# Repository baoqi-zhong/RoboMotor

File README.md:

# RoboMotor

**English** | [中文版](./README_CN.md)

**RoboMotor** is an open-source FOC motor driver project. It provides integrated hardware designs and control algorithms for robotics applications.

## Key Features

- **Hardware Specs**: 4-to-6 layer PCBs designed for 20A-40A continuous current at 24V.
- **Control Algorithm**: Field-Oriented Control (FOC) with current, speed, and position loops.
- **Validation**: Designs tested in RoboMaster environments.

## Hardware

Designed with **KiCad 8**.
For detailed specifications, schematics, and measured performance, please visit the [Hardware](./Hardware/README.md) directory or click on a specific project below.

| Project Name | Target Motor | Key Specs | Core |
| :--- | :--- | :--- | :--- |
| [**RoboMotor-DJI-M3508**](./Hardware/RoboMotor-DJI-M3508/) | [DJI M3508](https://www.robomaster.com/en-US/products/components/general/M3508) | **24V 20A**, 6-Layer, Sin/Cos Encoder | STSPIN32G4 |
| [**RoboMotor-GIM6010-V2**](./Hardware/RoboMotor-GIM6010-V2/) | [GIM6010-8](https://steadywin-motor.com/products/built-in-star-gear-motor-motor-robot-joint-driver-actuator-controller-motor) | **24V 40A**, Dual Encoder Support | STSPIN32G4 |
| [**RoboMotor-GIM6010-V2-Encoder**](./Hardware/RoboMotor-GIM6010-V2-Encoder/) | GIM6010-8 | Magnetic Output Encoder PCB | MA730 |
| [**RoboMotor-GIM6010**](./Hardware/RoboMotor-GIM6010/) | GIM6010-8 | *Legacy Reference Design* | STM32G431 + FD6288 |

## Software

The FOC control algorithm is developed for the **STM32G4** series.

### Features
- **FOC Implementation**: Sensor-based Field-Oriented Control with Flux/Torque decoupling and BEMF feedforward compensation.
- **Control Loops**: 17Khz inner Current loop + outer 4Khz Speed loop + 1Khz Position loop.
- **Connectivity**:
  - **CAN Bus**: Compatible with DJI RoboMaster protocols (M3508/C620).
  - **Custom Protocol**: Extended commands for parameter tuning and telemetry.
- **Additional Functions**:
  - **Auto-Calibration**: Routines for encoder offset and motor parameter identification.
  - **Safety Mechanisms**: Error handling (Over-current, Over/under voltage, Over-temp) with auto-recovery modes.
  - **Feedback Support**: Support for SPI magnetic encoders and analog inputs.

*Find the source code and documentation in the `Software/` directory.*

## License

This project is released under the MIT License.  
See [LICENSE](./LICENSE) for details.

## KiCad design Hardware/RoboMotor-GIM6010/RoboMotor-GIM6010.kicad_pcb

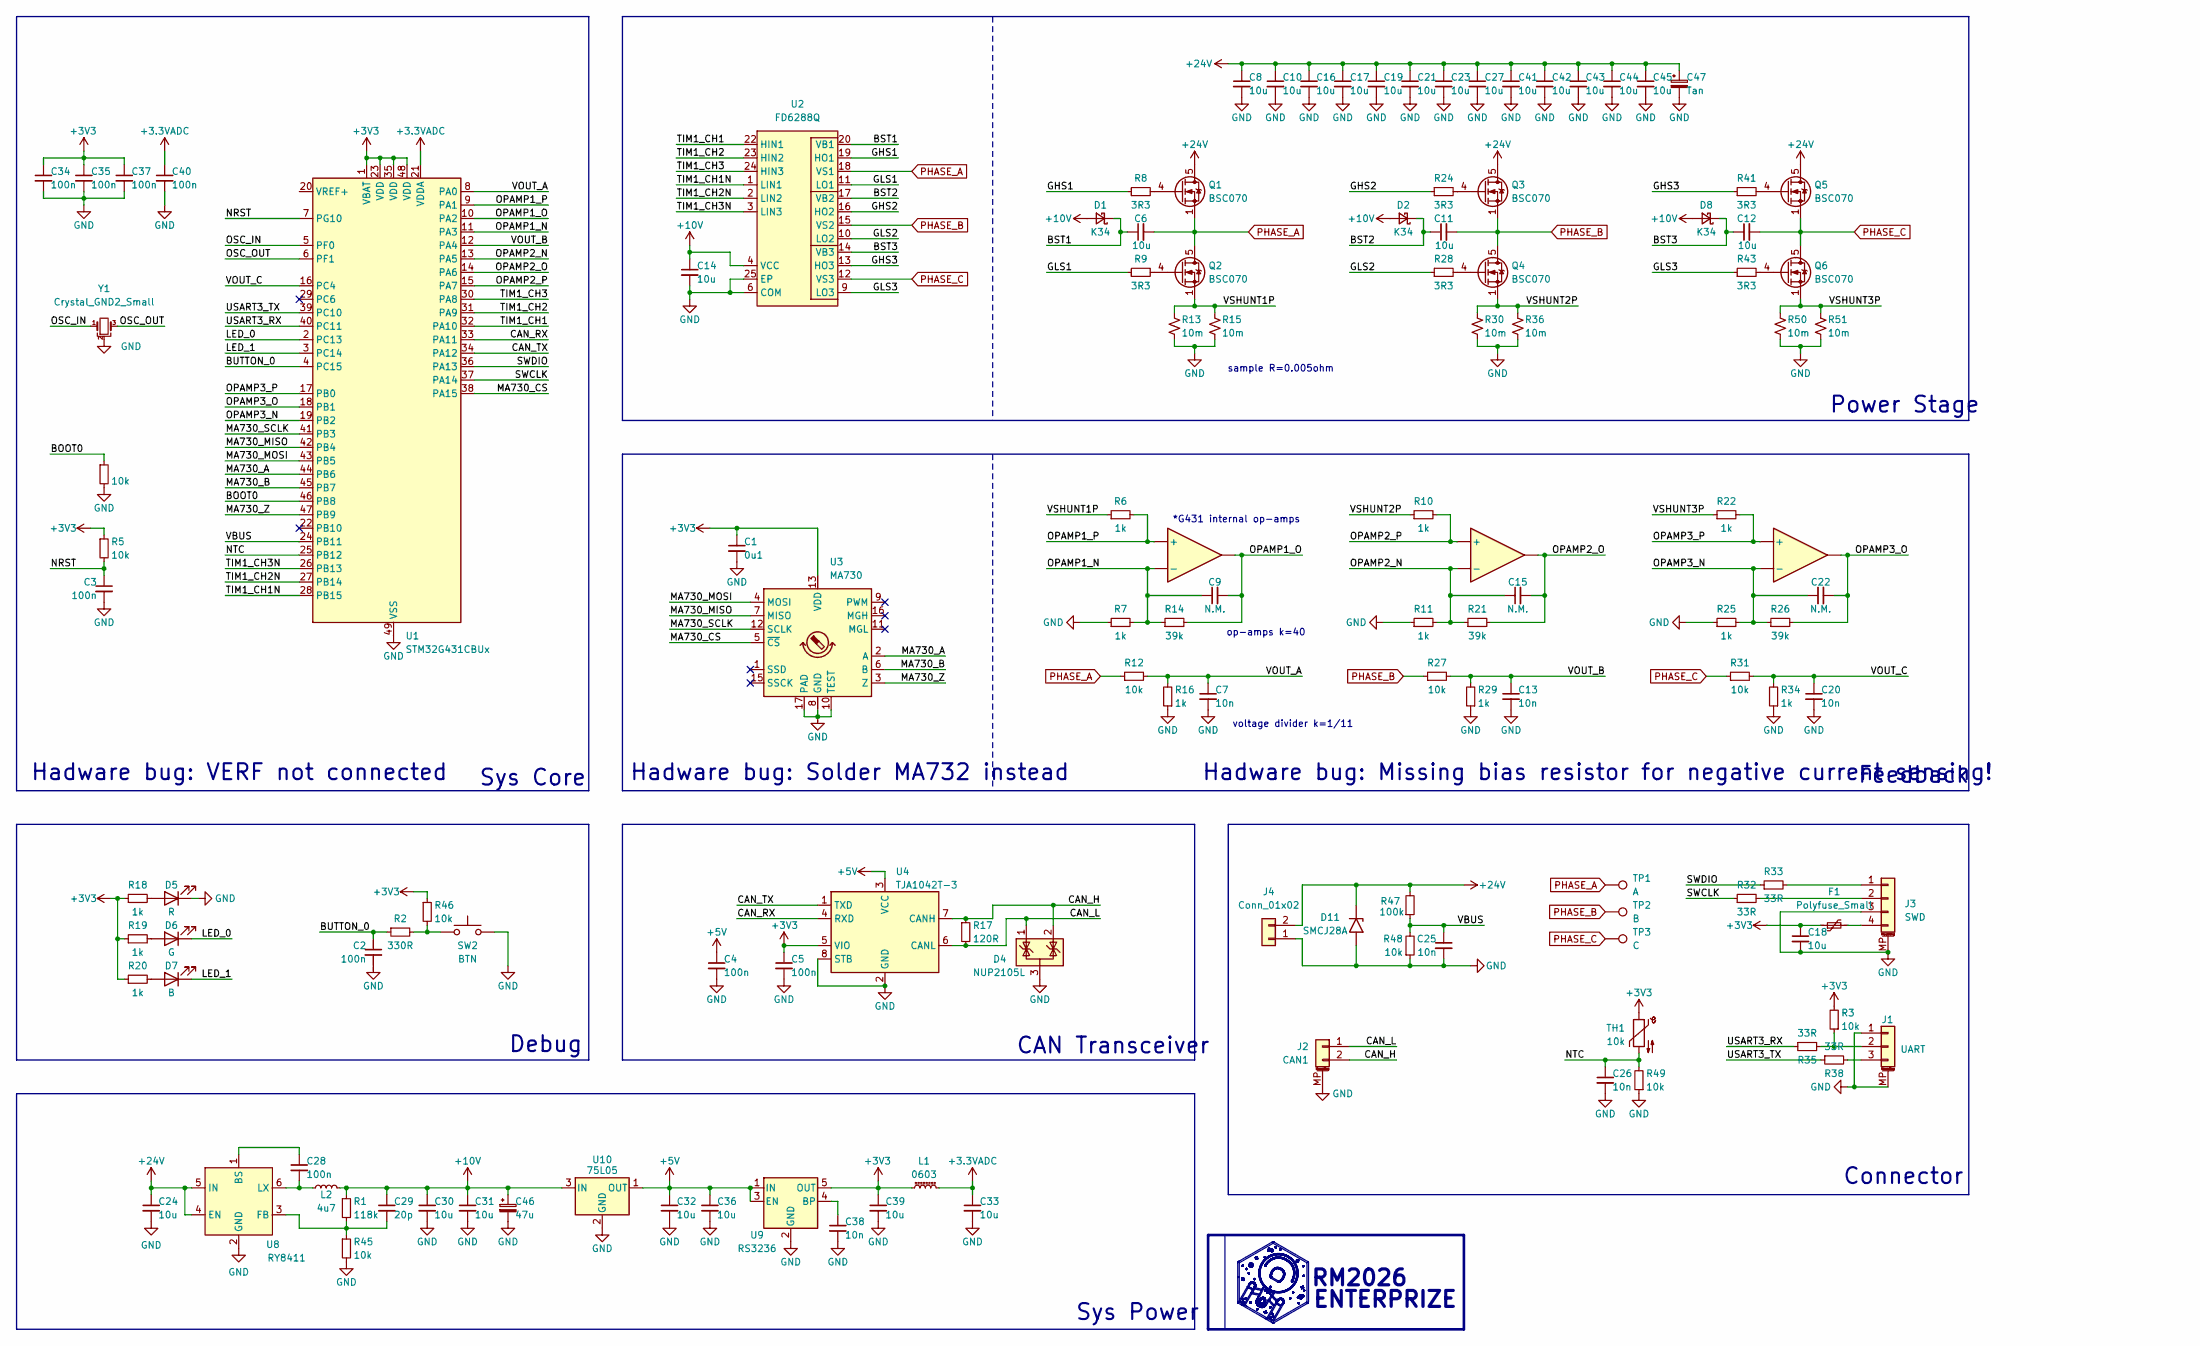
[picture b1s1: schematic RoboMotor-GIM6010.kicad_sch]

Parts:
C1: 0u1; C_0603_1608Metric
C2, C3, C4, C5, C28, C34, C35, C37, C40: 100n; C_0603_1608Metric
C6, C11, C12, C14, C18, C32, C33, C36, C39: 10u; C_0603_1608Metric
C7, C13, C20, C25, C26, C38: 10n; C_0603_1608Metric
C8, C10, C16, C17, C19, C21, C23, C24, C27, C30, C31, C41, C42, C43, C44, C45: 10u; C_1206_3216Metric
C9, C15, C22: N.M.; C_0603_1608Metric
C29: 20p; C_0603_1608Metric
C46: 47u; CP_EIA-3216-18_Kemet-A_Pad1.58x1.35mm_HandSolder
C47: Tan; CP_EIA-7343-30_AVX-N
D1, D2, D8: K34; D_SOD-323_HandSoldering
D4: NUP2105L; SOT-23
D5: R; LED_Side_0802
D6: G; LED_Side_0802
D7: B; LED_Side_0802
D11: SMCJ28A; D_SMC
F1: Polyfuse_Small; Fuse_1206_3216Metric
J1: UART; JST_GH_SM03B-GHS-TB_1x03-1MP_P1.25mm_Horizontal
J2: CAN1; JST_GH_SM02B-GHS-TB_1x02-1MP_P1.25mm_Horizontal
J3: SWD; Molex_PicoBlade_53261-0471_1x04-1MP_P1.25mm_Horizontal
J4: Conn_01x02; AMASS_XT30PW-M_1x02_P2.50mm_Horizontal
L1: 0603; L_0603_1608Metric
L2: 4u7; L_Sunlord_MWSA0402S
Q1, Q2, Q3, Q4, Q5, Q6: BSC070; TDSON-8-1
R1: 118k; R_0603_1608Metric
R2: 330R; R_0603_1608Metric
R3, R4, R5, R12, R27, R31, R45, R46, R48, R49: 10k; R_0603_1608Metric
R6, R7, R10, R11, R16, R18, R19, R20, R22, R25, R29, R34: 1k; R_0603_1608Metric
R8, R9, R24, R28, R41, R43: 3R3; R_0603_1608Metric
R13, R15, R30, R36, R50, R51: 10m; R_1206_3216Metric
R14, R21, R26: 39k; R_0603_1608Metric
R17: 120R; R_0603_1608Metric
R32, R33, R35, R38: 33R; R_0603_1608Metric
R47: 100k; R_0603_1608Metric
SW2: BTN; Panasonic_EVQPUL_EVQPUC
TH1: 10k; TestPoint_2Pads_Pitch2.54mm_Drill0.8mm
TP1: A; TestPoint_Pad_4.0x4.0mm
TP2: B; TestPoint_Pad_4.0x4.0mm
TP3: C; TestPoint_Pad_4.0x4.0mm
U1: STM32G431CBUx; QFN-48-1EP_7x7mm_P0.5mm_EP5.6x5.6mm
U2: FD6288Q; QFN-24-1EP_4x4mm_P0.5mm_EP2.7x2.7mm
U3: MA730; QFN-16-1EP_3x3mm_P0.5mm_EP1.75x1.75mm
U4: TJA1042T-3; SOIC-8_3.9x4.9mm_P1.27mm
U5, U6, U7: type="X" model="OPAMP" lib=""
U8: RY8411; SOT-23-6
U9: RS3236; SOT-23-5
U10: 75L05; SOT-89-3
Y1: Crystal_GND2_Small; Resonator_SMD_Murata_CSTxExxV-3Pin_3.0x1.1mm

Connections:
+3.3VADC: C33.1, C40.1, L1.2, U1.21 (VDDA)
+3V3: C1.1, C5.1, C18.1, C34.1, C35.1, C37.1, C39.1, F1.1, L1.1, R3.2, R5.1, R18.1, R19.1, R20.1, R46.1, TH1.1, U1.1 (VBAT), U1.23 (VDD), U1.35 (VDD), U1.48 (VDD), U3.13 (VDD), U4.5 (VIO), U9.5 (OUT)
+5V: C4.1, C32.1, C36.1, U4.3 (VCC), U9.1 (IN), U9.3 (EN), U10.1 (OUT)
+10V: C14.1, C29.1, C30.1, C31.1, C46.1, D1.2 (A), D2.2 (A), D8.2 (A), L2.2, R1.1, U2.4 (VCC), U10.3 (IN)
+24V: C8.1, C10.1, C16.1, C17.1, C19.1, C21.1, C23.1, C24.1, C27.1, C41.1, C42.1, C43.1, C44.1, C45.1, C47.1, D11.1 (A1), J4.2, Q1.5 (D), Q3.5 (D), Q5.5 (D), R47.2, U8.4 (EN), U8.5 (IN)
/BOOT0: R4.1, U1.46 (PB8)
/BST1: C6.1, D1.1 (K), U2.20 (VB1)
/BST2: C11.1, D2.1 (K), U2.17 (VB2)
/BST3: C12.1, D8.1 (K), U2.14 (VB3)
/BUTTON_0: C2.1, R2.1, U1.4 (PC15)
/CAN_H: D4.2 (K), J2.2, R17.1, U4.7 (CANH)
/CAN_L: D4.1 (K), J2.1, R17.2, U4.6 (CANL)
/CAN_RX: U1.33 (PA11), U4.4 (RXD)
/CAN_TX: U1.34 (PA12), U4.1 (TXD)
/GHS1: R8.1, U2.19 (HO1)
/GHS2: R24.1, U2.16 (HO2)
/GHS3: R41.1, U2.13 (HO3)
/GLS1: R9.1, U2.11 (LO1)
/GLS2: R28.1, U2.10 (LO2)
/GLS3: R43.1, U2.9 (LO3)
/LED_0: D6.1 (K), U1.2 (PC13)
/LED_1: D7.1 (K), U1.3 (PC14)
/MA730_A: U1.44 (PB6), U3.2 (A)
/MA730_B: U1.45 (PB7), U3.6 (B)
/MA730_CS: U1.38 (PA15), U3.5 (~CS)
/MA730_MISO: U1.42 (PB4), U3.7 (MISO)
/MA730_MOSI: U1.43 (PB5), U3.4 (MOSI)
/MA730_SCLK: U1.41 (PB3), U3.12 (SCLK)
/MA730_Z: U1.47 (PB9), U3.3 (Z)
/NRST: C3.1, R5.2, U1.7 (PG10)
/NTC: C26.1, R49.2, TH1.2, U1.25 (PB12)
/OPAMP1_N: C9.1, R7.2, R14.1, U1.11 (PA3), U5.
/OPAMP1_O: C9.2, R14.2, U1.10 (PA2), U5.
/OPAMP1_P: R6.2, U1.9 (PA1), U5.
/OPAMP2_N: C15.1, R11.2, R21.1, U1.13 (PA5), U6.
/OPAMP2_O: C15.2, R21.2, U1.14 (PA6), U6.
/OPAMP2_P: R10.2, U1.15 (PA7), U6.
/OPAMP3_N: C22.1, R25.2, R26.1, U1.19 (PB2), U7.
/OPAMP3_O: C22.2, R26.2, U1.18 (PB1), U7.
/OPAMP3_P: R22.2, U1.17 (PB0), U7.
/OSC_IN: U1.5 (PF0), Y1.1
/OSC_OUT: U1.6 (PF1), Y1.3
/SWCLK: R32.1, U1.37 (PA14)
/SWDIO: R33.1, U1.36 (PA13)
/TIM1_CH1: U1.32 (PA10), U2.22 (HIN1)
/TIM1_CH1N: U1.28 (PB15), U2.1 (LIN1)
/TIM1_CH2: U1.31 (PA9), U2.23 (HIN2)
/TIM1_CH2N: U1.27 (PB14), U2.2 (LIN2)
/TIM1_CH3: U1.30 (PA8), U2.24 (HIN3)
/TIM1_CH3N: U1.26 (PB13), U2.3 (LIN3)
/USART3_RX: R35.1, U1.40 (PC11)
/USART3_TX: R38.1, U1.39 (PC10)
/VBUS: C25.1, R47.1, R48.2, U1.24 (PB11)
/VOUT_A: C7.1, R12.2, R16.2, U1.8 (PA0)
/VOUT_B: C13.1, R27.2, R29.2, U1.12 (PA4)
/VOUT_C: C20.1, R31.2, R34.2, U1.16 (PC4)
/VSHUNT1P: Q2.1 (S), Q2.2 (S), Q2.3 (S), R6.1, R13.1, R15.1
/VSHUNT2P: Q4.1 (S), Q4.2 (S), Q4.3 (S), R10.1, R30.1, R36.1
/VSHUNT3P: Q6.1 (S), Q6.2 (S), Q6.3 (S), R22.1, R50.1, R51.1
GND: C1.2, C2.2, C3.2, C4.2, C5.2, C7.2, C8.2, C10.2, C13.2, C14.2, C16.2, C17.2, C18.2, C19.2, C20.2, C21.2, C23.2, C24.2, C25.2, C26.2, C27.2, C30.2, C31.2, C32.2, C33.2, C34.2, C35.2, C36.2, C37.2, C38.2, C39.2, C40.2, C41.2, C42.2, C43.2, C44.2, C45.2, C46.2, C47.2, D4.3 (A), D5.1 (K), D11.2 (A2), J1.1, J1.MP (MountPin), J2.MP (MountPin), J3.3, J3.MP (MountPin), J4.1, R4.2, R7.1, R11.1, R13.2, R15.2, R16.1, R25.1, R29.1, R30.2, R34.1, R36.2, R45.2, R48.1, R49.1, R50.2, R51.2, SW2.2, U1.49 (VSS), U2.6 (COM), U2.25 (EP), U3.8 (GND), U3.10 (TEST), U3.17 (PAD), U4.2 (GND), U4.8 (STB), U8.2 (GND), U9.2 (GND), U10.2 (GND), Y1.2
unnamed: D5.2 (A), R18.2
unnamed: D6.2 (A), R19.2
unnamed: D7.2 (A), R20.2
unnamed: J1.2, R3.1, R35.2
unnamed: J1.3, R38.2
unnamed: J3.1, R33.2
unnamed: J3.2, R32.2
unnamed: F1.2, J3.4
unnamed: Q1.4 (G), R8.2
unnamed: Q2.4 (G), R9.2
unnamed: Q3.4 (G), R24.2
unnamed: Q4.4 (G), R28.2
unnamed: Q5.4 (G), R41.2
unnamed: Q6.4 (G), R43.2
unnamed: R2.2, R46.2, SW2.1
unnamed: C28.1, U8.1 (BS)
unnamed: C29.2, R1.2, R45.1, U8.3 (FB)
unnamed: C28.2, L2.1, U8.6 (LX)
unnamed: C38.1, U9.4 (BP)
PHASE_A: C6.2, Q1.1 (S), Q1.2 (S), Q1.3 (S), Q2.5 (D), R12.1, TP1.1, U2.18 (VS1)
PHASE_B: C11.2, Q3.1 (S), Q3.2 (S), Q3.3 (S), Q4.5 (D), R27.1, TP2.1, U2.15 (VS2)
PHASE_C: C12.2, Q5.1 (S), Q5.2 (S), Q5.3 (S), Q6.5 (D), R31.1, TP3.1, U2.12 (VS3)

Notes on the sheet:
op-amps k=40
Hadware bug: VERF not connected
Hadware bug: Missing bias resistor for negative current sensing!
RM2026
Sys Power
CAN Transceiver
ENTERPRIZE
Connector
Hadware bug: Solder MA732 instead
sample R=0.005ohm
Sys Core
*G431 internal op-amps
Debug
voltage divider k=1/11
Power Stage
Feedback

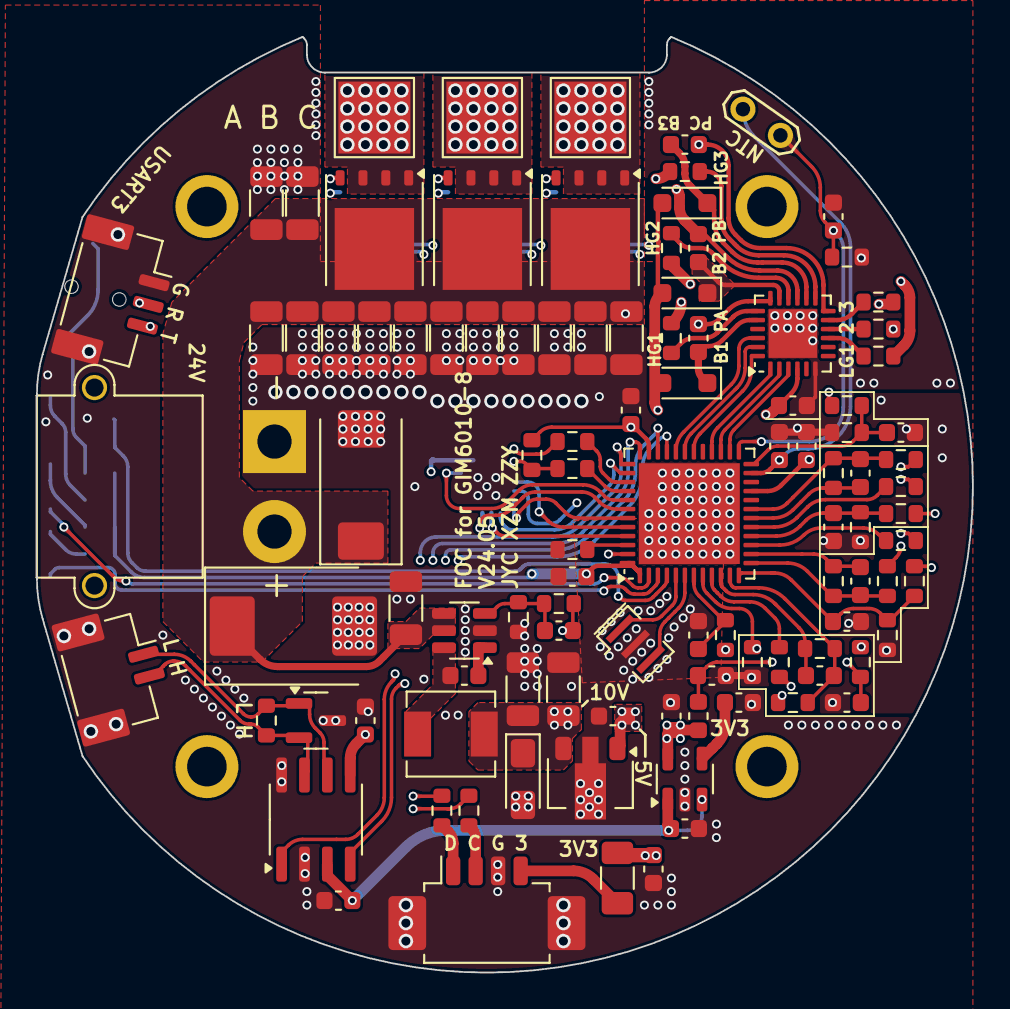
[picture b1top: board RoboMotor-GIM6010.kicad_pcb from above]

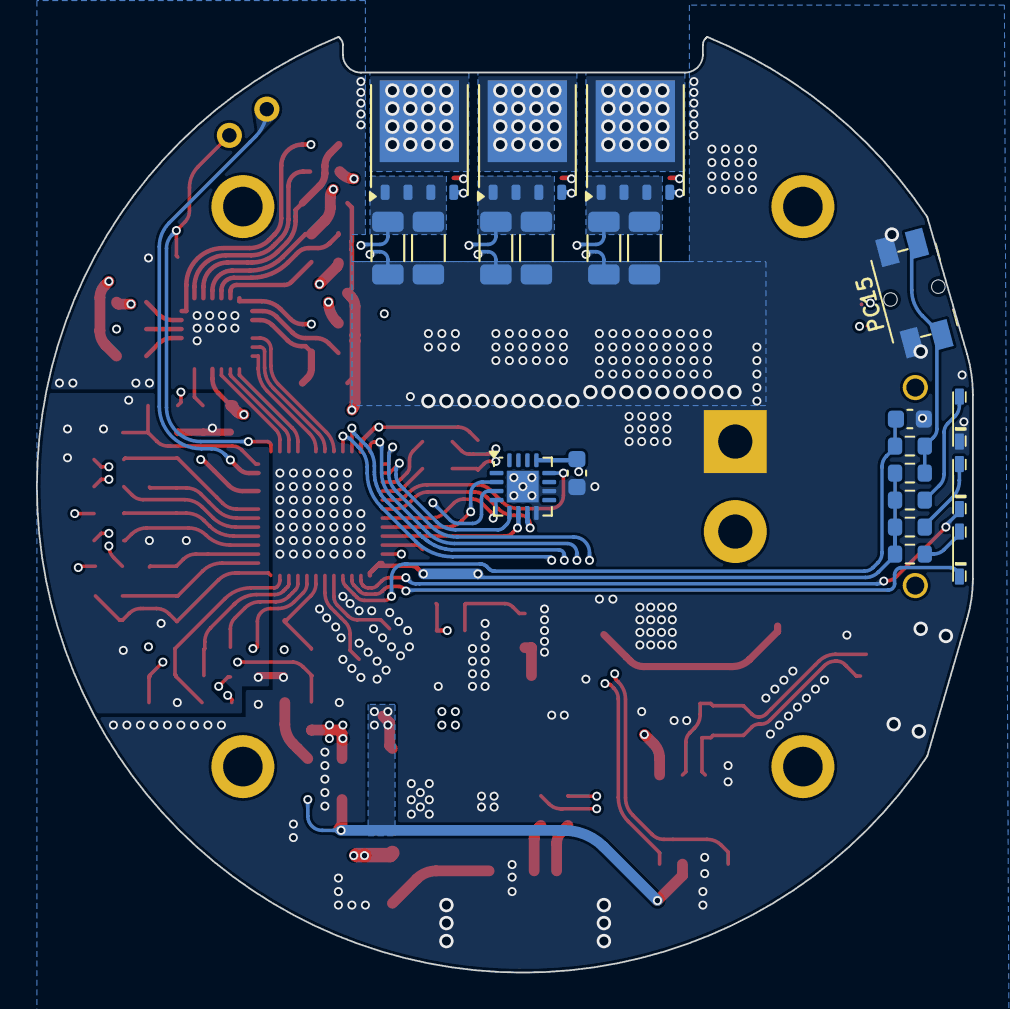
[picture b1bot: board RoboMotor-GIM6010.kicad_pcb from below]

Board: 4 copper layers, 52.0 x 52.0 mm, 130 parts (21 on the bottom side), 82 nets.

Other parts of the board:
H1, H2, H3, H4: MountingHole_Pad; MountingHole_2.2mm_M2_ISO7380_Pad

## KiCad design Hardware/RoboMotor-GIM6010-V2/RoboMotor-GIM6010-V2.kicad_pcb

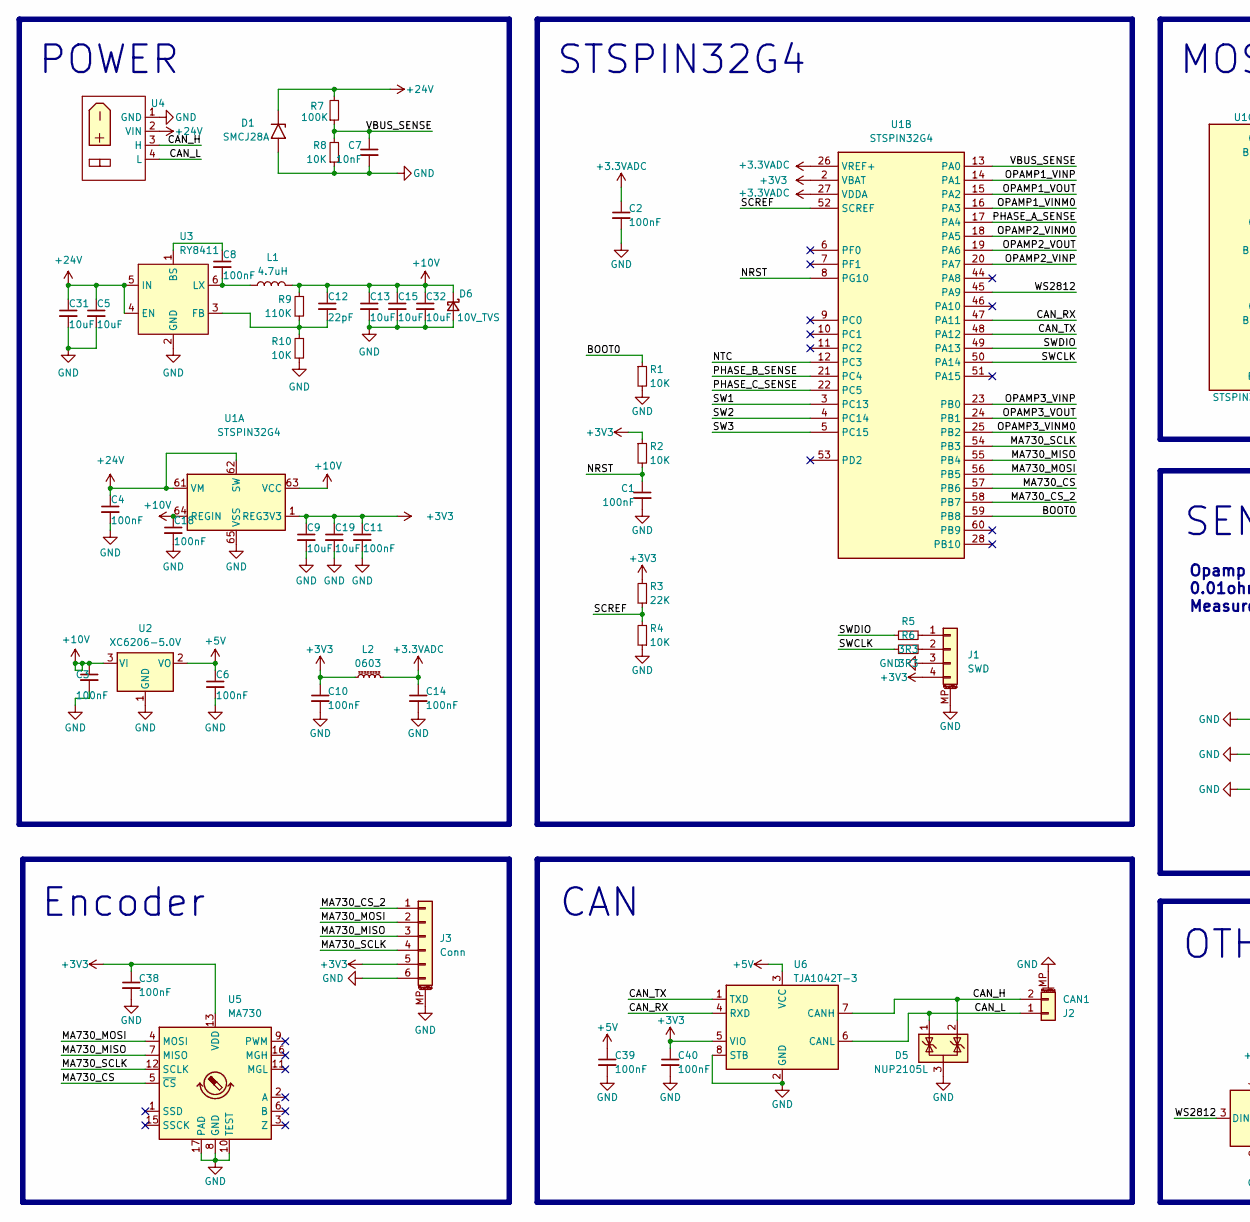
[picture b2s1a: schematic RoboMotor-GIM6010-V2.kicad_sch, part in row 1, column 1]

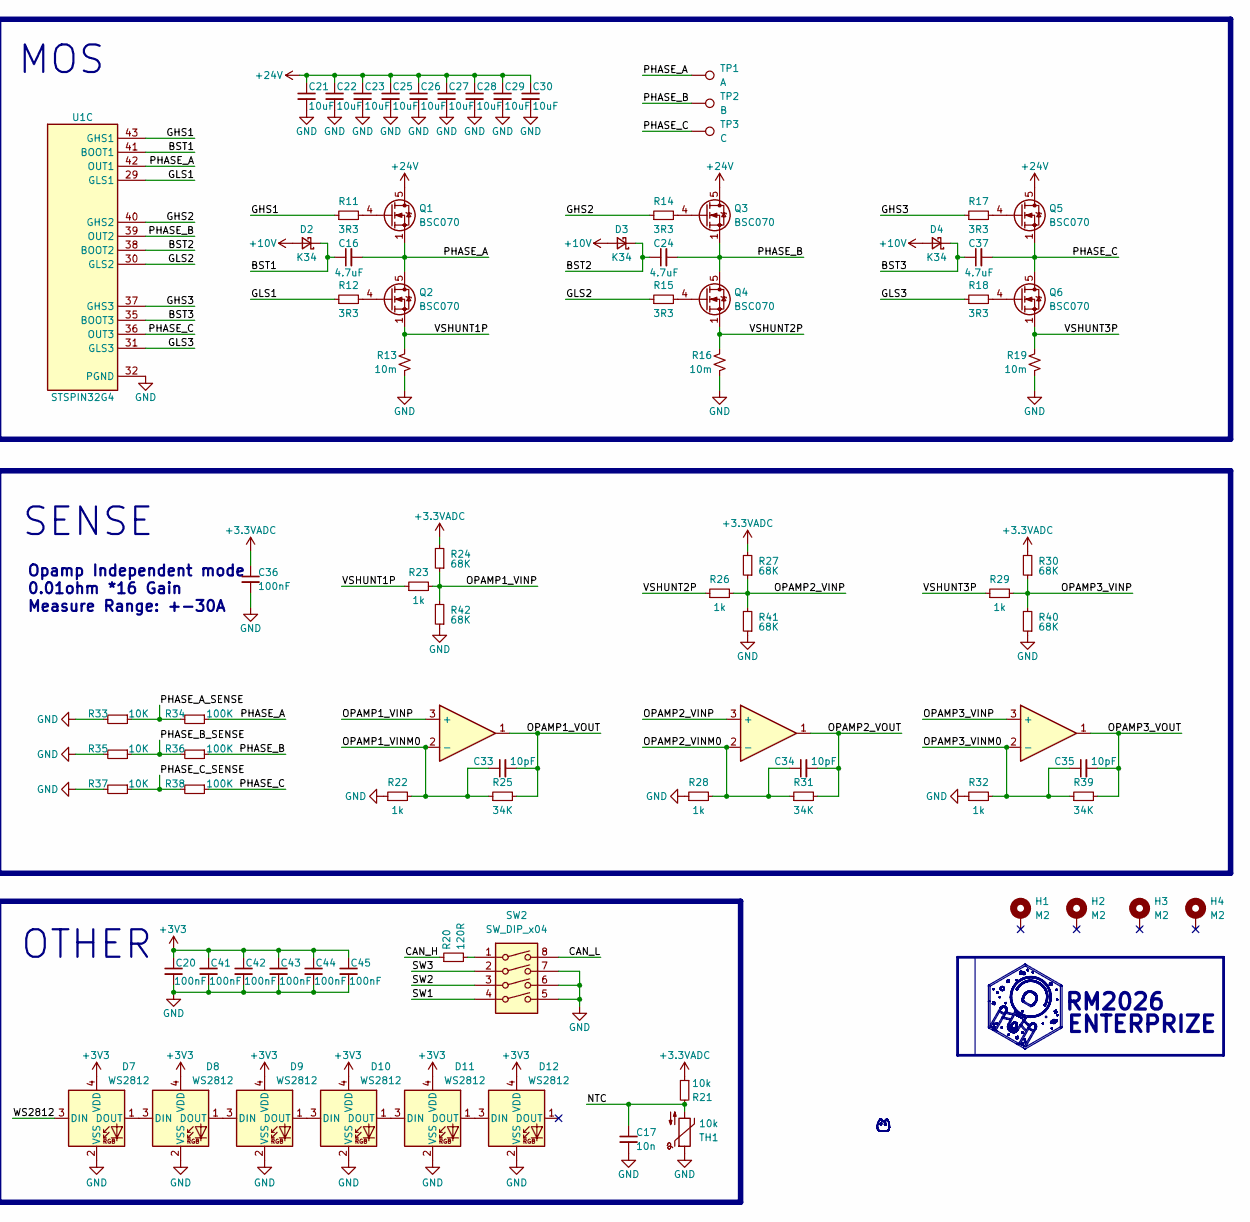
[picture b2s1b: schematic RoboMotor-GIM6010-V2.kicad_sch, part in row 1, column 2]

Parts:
C1, C2, C3, C4, C6, C8, C10, C11, C14, C18, C20, C36, C38, C39, C40, C41, C42, C43, C44, C45: 100nF; C_0603_1608Metric
C5, C13, C15, C21, C22, C23, C25, C26, C27, C28, C29, C30, C31, C32: 10uF; C_1206_3216Metric
C7: 10nF; C_0603_1608Metric
C9, C19: 10uF; C_0603_1608Metric
C12: 22pF; C_0603_1608Metric
C16, C24, C37: 4.7uF; C_0603_1608Metric
C17: 10n; C_0603_1608Metric
C33, C34, C35: 10pF; C_0402_1005Metric
D1: SMCJ28A; D_SMA
D2, D3, D4: K34; D_SOD-323_HandSoldering
D5: NUP2105L; SOT-23
D6: 10V_TVS; D_SMF
D7, D8, D9, D10, D11, D12: WS2812; LED_WS2812B-2020_PLCC4_2.0x2.0mm
H1, H2, H3, H4: M2; MountingHole_2.2mm_M2_DIN965_Pad_TopBottom
J1: SWD; Molex_PicoBlade_53261-0471_1x04-1MP_P1.25mm_Horizontal
J2: CAN1; JST_GH_SM02B-GHS-TB_1x02-1MP_P1.25mm_Horizontal
J3: Conn; TE_0-1734839-6_1x06-1MP_P0.5mm_Horizontal
L1: 4.7uH; L_Neosid_SMS-ME3015
L2: 0603; L_0603_1608Metric
Q1, Q2, Q3, Q4, Q5, Q6: BSC070; TDSON-8-1
R1, R2, R4, R8, R10, R33, R35, R37: 10K; R_0603_1608Metric
R3: 22K; R_0603_1608Metric
R5, R6, R11, R12, R14, R15, R17, R18: 3R3; R_0603_1608Metric
R7, R34, R36, R38: 100K; R_0603_1608Metric
R9: 110K; R_0603_1608Metric
R13, R16, R19: 10m; R_2512_6332Metric
R20: 120R; R_0603_1608Metric
R21: 10k; R_0603_1608Metric
R22, R23, R26, R28, R29, R32: 1k; R_0402_1005Metric
R24, R27, R30, R40, R41, R42: 68K; R_0402_1005Metric
R25, R31, R39: 34K; R_0402_1005Metric
SW2: SW_DIP_x04; SW_DIP_SPSTx04_Slide_Copal_CHS-04B_W7.62mm_P1.27mm
TH1: 10k; TestPoint_2Pads_Pitch2.54mm_Drill0.8mm
TP1: A; TestPoint_Pad_4.0x4.0mm
TP2: B; TestPoint_Pad_4.0x4.0mm
TP3: C; TestPoint_Pad_4.0x4.0mm
U1: STSPIN32G4; QFN-64-1EP_9x9mm_P0.5mm_EP4.35x4.35mm
U2: XC6206-5.0V; SOT-23-3
U3: RY8411; SOT-23-6
U4: AMASS_XT30PW(2+2)-M_1x02_P2.50mm_Horizontal
U5: MA730; QFN-16-1EP_3x3mm_P0.5mm_EP1.75x1.75mm
U6: TJA1042T-3; SOIC-8_3.9x4.9mm_P1.27mm
U7, U8, U9: (no value)

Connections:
+3.3VADC: C2.1, C14.1, C36.1, L2.2, R21.1, R24.2, R27.2, R30.2, U1.26 (VREF+), U1.27 (VDDA)
+3V3: C9.1, C10.1, C11.1, C19.1, C20.1, C38.1, C40.1, C41.1, C42.1, C43.1, C44.1, C45.1, D7.4 (VDD), D8.4 (VDD), D9.4 (VDD), D10.4 (VDD), D11.4 (VDD), D12.4 (VDD), J1.4, J3.5, L2.1, R2.1, R3.2, U1.1 (REG3V3), U1.2 (VBAT), U5.13 (VDD), U6.5 (VIO)
+5V: C6.1, C39.1, U2.2 (VO), U6.3 (VCC)
+10V: C3.1, C12.1, C13.1, C15.1, C18.1, C32.1, D2.2 (A), D3.2 (A), D4.2 (A), D6.1 (K), L1.2, R9.1, U1.63 (VCC), U1.64 (REGIN), U2.3 (VI)
+24V: C4.1, C5.1, C21.1, C22.1, C23.1, C25.1, C26.1, C27.1, C28.1, C29.1, C30.1, C31.1, D1.1 (A1), Q1.5 (D), Q3.5 (D), Q5.5 (D), R7.2, U1.61 (VM), U1.62 (SW), U3.4 (EN), U3.5 (IN), U4.2 (VIN)
/BOOT0: R1.1, U1.59 (PB8)
/BST1: C16.1, D2.1 (K), U1.41 (BOOT1)
/BST2: C24.1, D3.1 (K), U1.38 (BOOT2)
/BST3: C37.1, D4.1 (K), U1.35 (BOOT3)
/CAN_H: D5.2 (K), J2.2, R20.1, U4.3 (H), U6.7 (CANH)
/CAN_L: D5.1 (K), J2.1, SW2.8, U4.4 (L), U6.6 (CANL)
/CAN_RX: U1.47 (PA11), U6.4 (RXD)
/CAN_TX: U1.48 (PA12), U6.1 (TXD)
/GHS1: R11.1, U1.43 (GHS1)
/GHS2: R14.1, U1.40 (GHS2)
/GHS3: R17.1, U1.37 (GHS3)
/GLS1: R12.1, U1.29 (GLS1)
/GLS2: R15.1, U1.30 (GLS2)
/GLS3: R18.1, U1.31 (GLS3)
/MA730_CS: U1.57 (PB6), U5.5 (~CS)
/MA730_CS_2: J3.1, U1.58 (PB7)
/MA730_MISO: J3.3, U1.55 (PB4), U5.7 (MISO)
/MA730_MOSI: J3.2, U1.56 (PB5), U5.4 (MOSI)
/MA730_SCLK: J3.4, U1.54 (PB3), U5.12 (SCLK)
/NRST: C1.1, R2.2, U1.8 (PG10)
/NTC: C17.1, R21.2, TH1.2, U1.12 (PC3)
/OPAMP1_VINM0: C33.1, R22.2, R25.1, U1.16 (PA3), U7.2 (-)
/OPAMP1_VINP: R23.2, R24.1, R42.2, U1.14 (PA1), U7.3 (+)
/OPAMP1_VOUT: C33.2, R25.2, U1.15 (PA2), U7.1
/OPAMP2_VINM0: C34.1, R28.2, R31.1, U1.18 (PA5), U8.2 (-)
/OPAMP2_VINP: R26.2, R27.1, R41.2, U1.20 (PA7), U8.3 (+)
/OPAMP2_VOUT: C34.2, R31.2, U1.19 (PA6), U8.1
/OPAMP3_VINM0: C35.1, R32.2, R39.1, U1.25 (PB2), U9.2 (-)
/OPAMP3_VINP: R29.2, R30.1, R40.2, U1.23 (PB0), U9.3 (+)
/OPAMP3_VOUT: C35.2, R39.2, U1.24 (PB1), U9.1
/PHASE_A: C16.2, Q1.1 (S), Q1.2 (S), Q1.3 (S), Q2.5 (D), R34.1, TP1.1, U1.42 (OUT1)
/PHASE_A_SENSE: R33.1, R34.2, U1.17 (PA4)
/PHASE_B: C24.2, Q3.1 (S), Q3.2 (S), Q3.3 (S), Q4.5 (D), R36.1, TP2.1, U1.39 (OUT2)
/PHASE_B_SENSE: R35.1, R36.2, U1.21 (PC4)
/PHASE_C: C37.2, Q5.1 (S), Q5.2 (S), Q5.3 (S), Q6.5 (D), R38.1, TP3.1, U1.36 (OUT3)
/PHASE_C_SENSE: R37.1, R38.2, U1.22 (PC5)
/SCREF: R3.1, R4.2, U1.52 (SCREF)
/SW1: SW2.4, U1.3 (PC13)
/SW2: SW2.3, U1.4 (PC14)
/SW3: SW2.2, U1.5 (PC15)
/SWCLK: R6.1, U1.50 (PA14)
/SWDIO: R5.1, U1.49 (PA13)
/VBUS_SENSE: C7.1, R7.1, R8.2, U1.13 (PA0)
/VSHUNT1P: Q2.1 (S), Q2.2 (S), Q2.3 (S), R13.1, R23.1
/VSHUNT2P: Q4.1 (S), Q4.2 (S), Q4.3 (S), R16.1, R26.1
/VSHUNT3P: Q6.1 (S), Q6.2 (S), Q6.3 (S), R19.1, R29.1
/WS2812: D7.3 (DIN), U1.45 (PA9)
GND: C1.2, C2.2, C3.2, C4.2, C5.2, C6.2, C7.2, C9.2, C10.2, C11.2, C13.2, C14.2, C15.2, C17.2, C18.2, C19.2, C20.2, C21.2, C22.2, C23.2, C25.2, C26.2, C27.2, C28.2, C29.2, C30.2, C31.2, C32.2, C36.2, C38.2, C39.2, C40.2, C41.2, C42.2, C43.2, C44.2, C45.2, D1.2 (A2), D5.3 (A), D6.2 (A), D7.2 (VSS), D8.2 (VSS), D9.2 (VSS), D10.2 (VSS), D11.2 (VSS), D12.2 (VSS), J1.3, J1.MP (MountPin), J2.MP (MountPin), J3.6, J3.MP (MountPin), R1.2, R4.1, R8.1, R10.2, R13.2, R16.2, R19.2, R22.1, R28.1, R32.1, R33.2, R35.2, R37.2, R40.1, R41.1, R42.1, SW2.5, SW2.6, SW2.7, TH1.1, U1.32 (PGND), U1.65 (VSS), U2.1 (GND), U3.2 (GND), U4.1 (GND), U5.8 (GND), U5.10 (TEST), U5.17 (PAD), U6.2 (GND), U6.8 (STB)
unnamed: D7.1 (DOUT), D8.3 (DIN)
unnamed: D8.1 (DOUT), D9.3 (DIN)
unnamed: D9.1 (DOUT), D10.3 (DIN)
unnamed: D10.1 (DOUT), D11.3 (DIN)
unnamed: D11.1 (DOUT), D12.3 (DIN)
unnamed: J1.1, R5.2
unnamed: J1.2, R6.2
unnamed: Q1.4 (G), R11.2
unnamed: Q2.4 (G), R12.2
unnamed: Q3.4 (G), R14.2
unnamed: Q4.4 (G), R15.2
unnamed: Q5.4 (G), R17.2
unnamed: Q6.4 (G), R18.2
unnamed: R20.2, SW2.1
unnamed: C8.1, U3.1 (BS)
unnamed: C12.2, R9.2, R10.1, U3.3 (FB)
unnamed: C8.2, L1.1, U3.6 (LX)

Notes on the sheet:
CAN
ENTERPRIZE
RM2026
SENSE
MOS
STSPIN32G4
Encoder
OTHER
POWER
Opamp Independent mode 0.01ohm *16 Gain Measure Range: +-30A

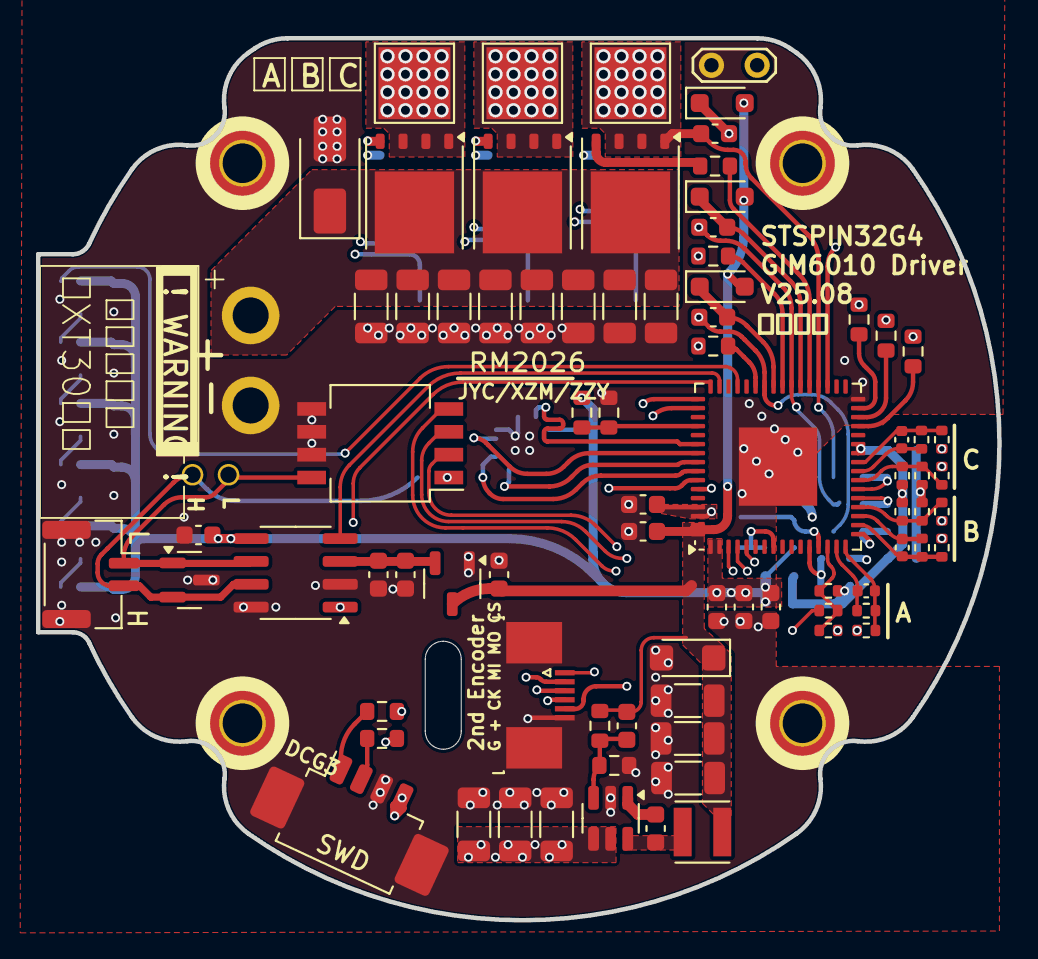
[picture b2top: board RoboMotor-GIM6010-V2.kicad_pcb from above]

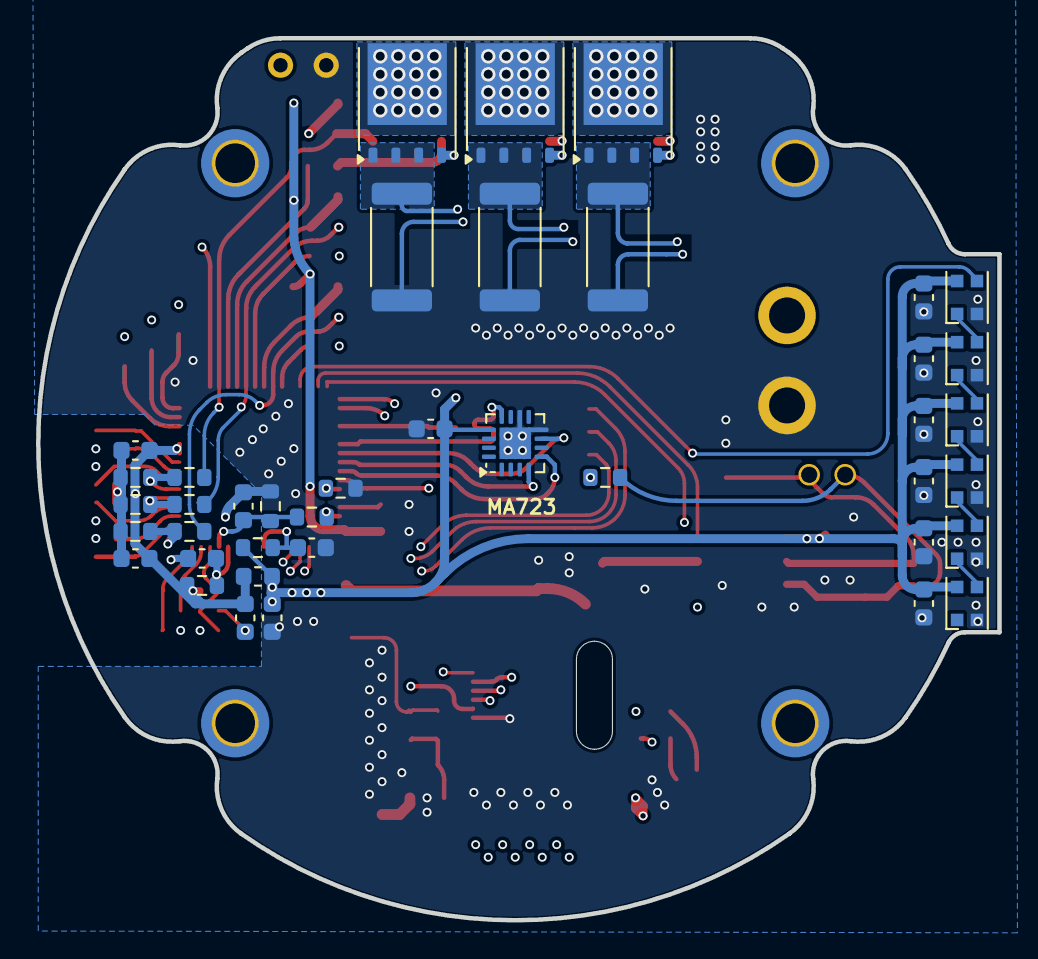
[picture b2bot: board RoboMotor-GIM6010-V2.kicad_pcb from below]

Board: 4 copper layers, 53.4 x 49.0 mm, 125 parts (40 on the bottom side), 70 nets.

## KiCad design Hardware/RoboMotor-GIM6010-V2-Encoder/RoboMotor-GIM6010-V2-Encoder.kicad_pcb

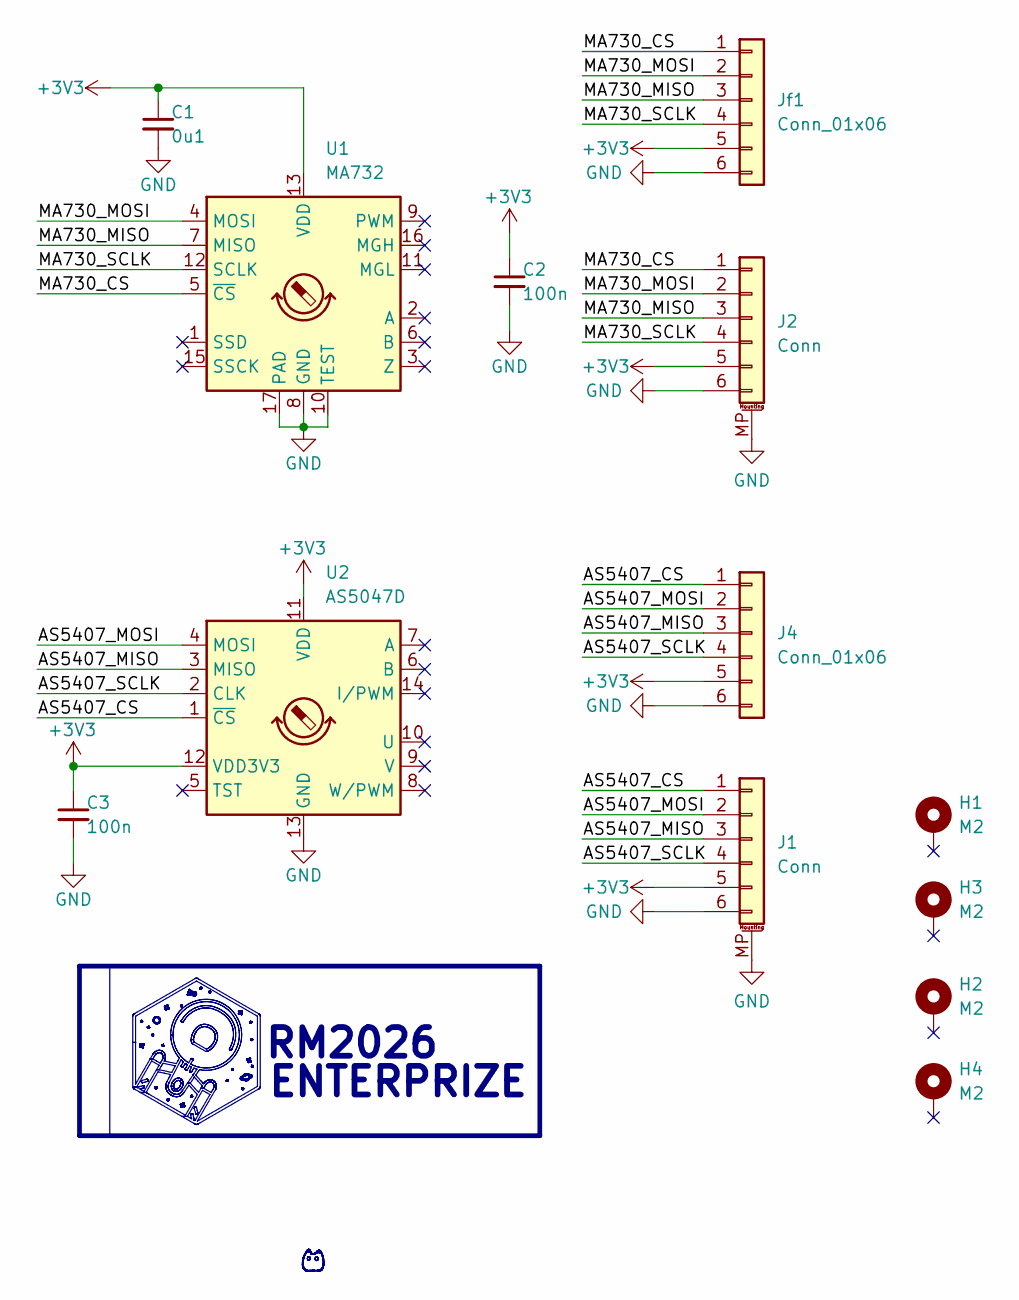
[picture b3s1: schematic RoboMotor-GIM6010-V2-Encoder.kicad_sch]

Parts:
C1: 0u1; C_0603_1608Metric
C2, C3: 100n; C_0603_1608Metric
H1, H2, H3, H4: M2; MountingHole_2.2mm_M2_DIN965_Pad_TopBottom
J1, J2: Conn; TE_0-1734839-6_1x06-1MP_P0.5mm_Horizontal
J4: Conn_01x06; PinHeader_1x06_P1.27mm_Vertical
Jf1: Conn_01x06; PinHeader_1x06_P1.27mm_Vertical
U1: MA732; QFN-16-1EP_3x3mm_P0.5mm_EP1.75x1.75mm
U2: AS5047D; TSSOP-14_4.4x5mm_P0.65mm

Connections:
+3V3: C1.1, C2.1, C3.1, J1.5, J2.5, J4.5, Jf1.5, U1.13 (VDD), U2.11 (VDD), U2.12 (VDD3V3)
/AS5407_CS: J1.1, J4.1, U2.1 (~CS)
/AS5407_MISO: J1.3, J4.3, U2.3 (MISO)
/AS5407_MOSI: J1.2, J4.2, U2.4 (MOSI)
/AS5407_SCLK: J1.4, J4.4, U2.2 (CLK)
/MA730_CS: J2.1, Jf1.1, U1.5 (~CS)
/MA730_MISO: J2.3, Jf1.3, U1.7 (MISO)
/MA730_MOSI: J2.2, Jf1.2, U1.4 (MOSI)
/MA730_SCLK: J2.4, Jf1.4, U1.12 (SCLK)
GND: C1.2, C2.2, C3.2, J1.6, J1.MP (MountPin), J2.6, J2.MP (MountPin), J4.6, Jf1.6, U1.8 (GND), U1.10 (TEST), U1.17 (PAD), U2.13 (GND)

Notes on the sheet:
ENTERPRIZE
RM2026

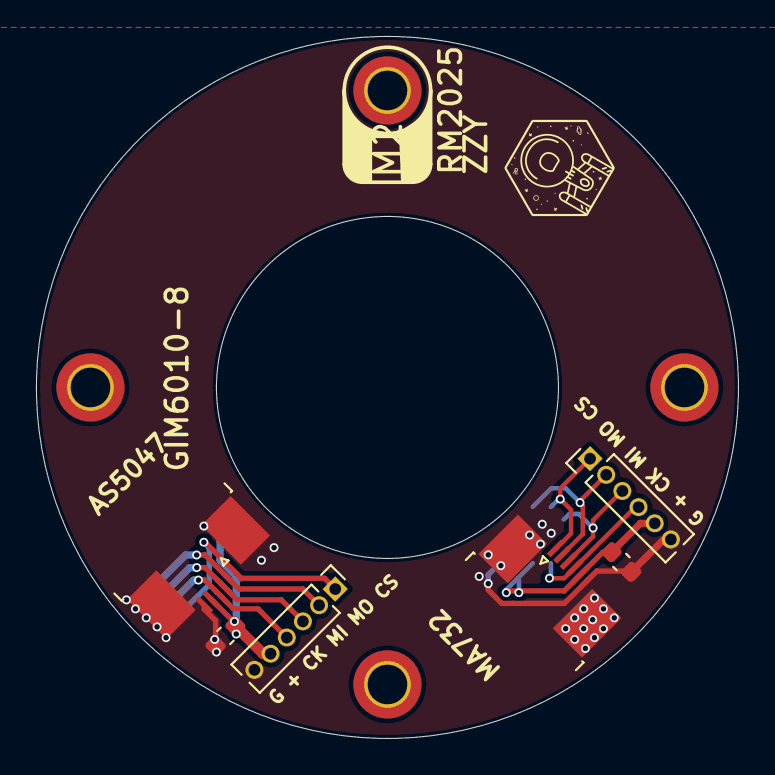
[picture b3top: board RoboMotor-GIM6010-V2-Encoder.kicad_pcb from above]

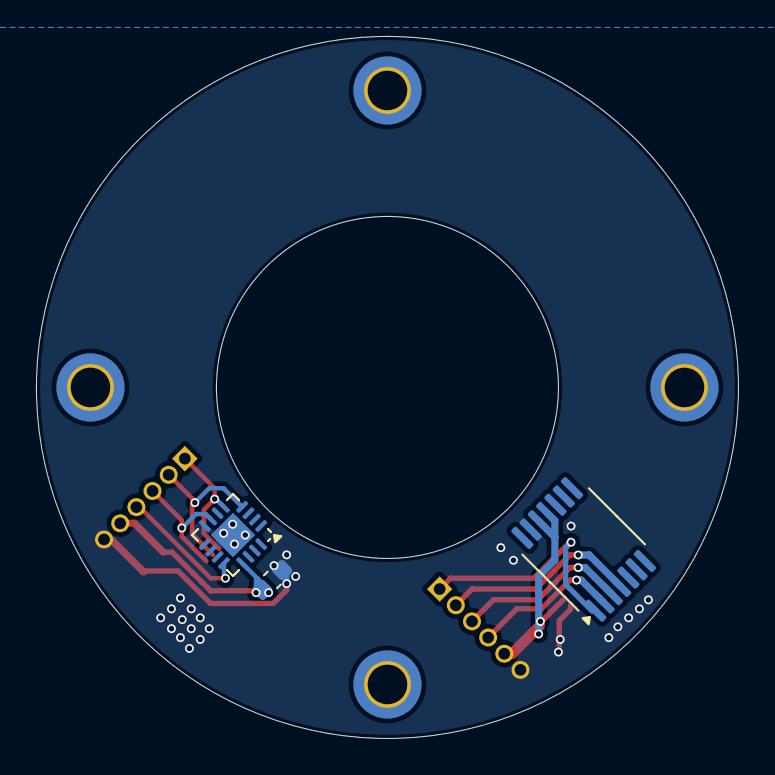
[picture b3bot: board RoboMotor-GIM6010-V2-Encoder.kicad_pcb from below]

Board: 2 copper layers, 39.0 x 39.0 mm, 13 parts (3 on the bottom side), 10 nets.
